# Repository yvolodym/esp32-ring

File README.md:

# esp32-ring

https://github.com/espressif/esp-idf/tree/v5.4/examples/peripherals/lcd/i2c_oled/main

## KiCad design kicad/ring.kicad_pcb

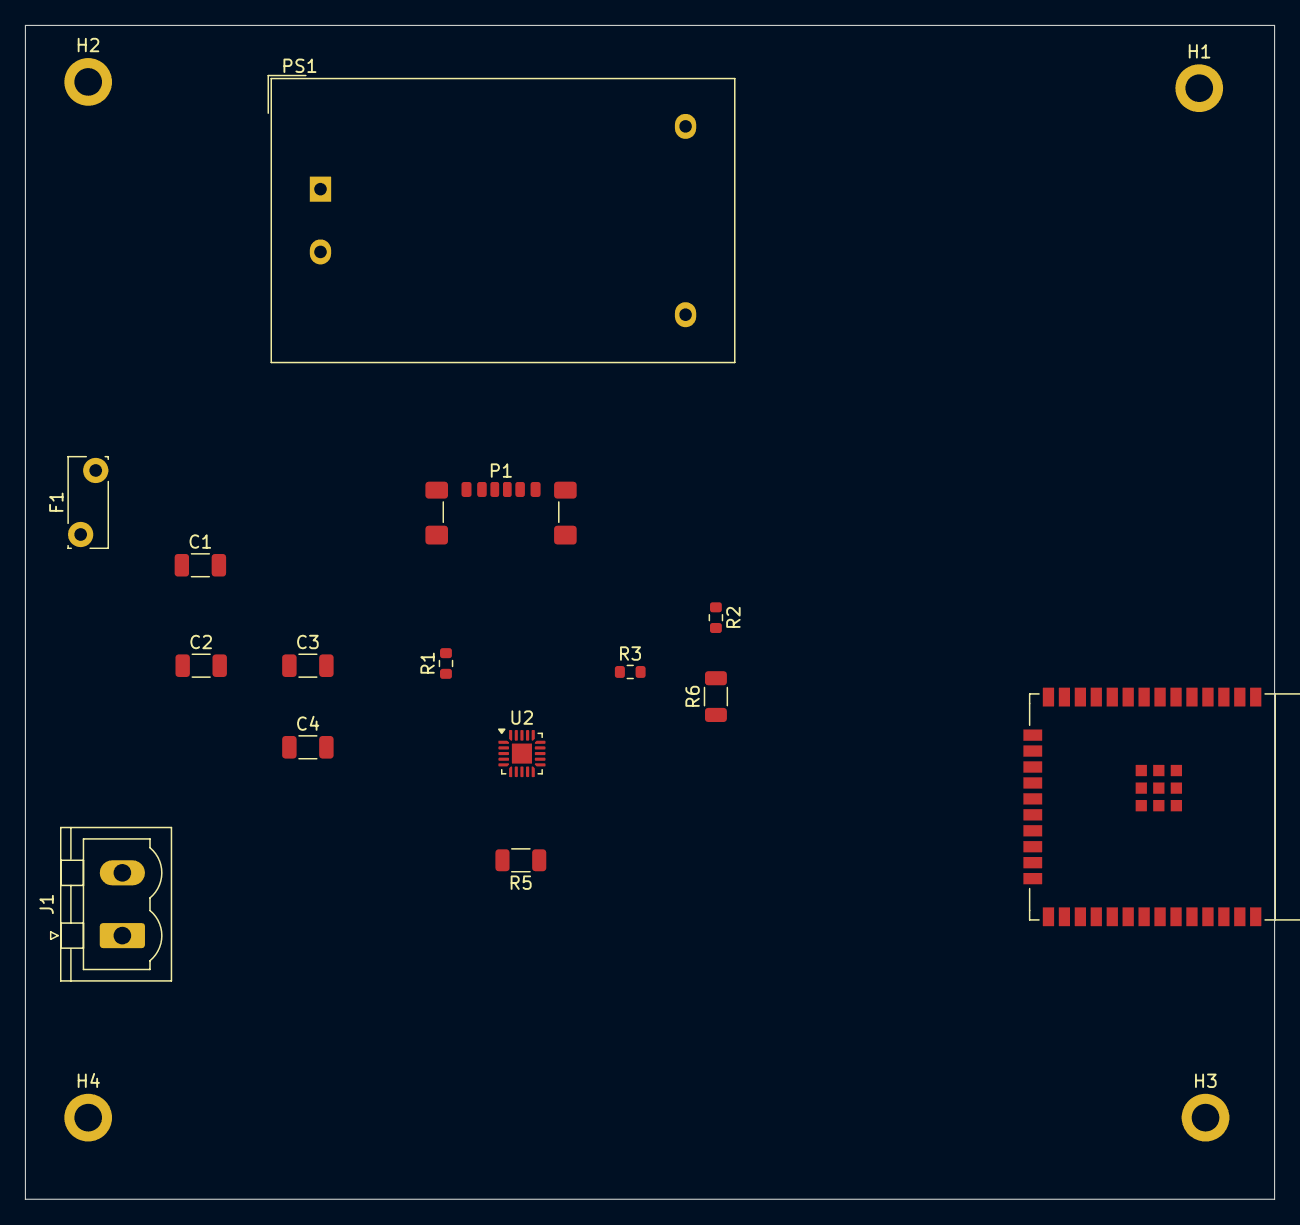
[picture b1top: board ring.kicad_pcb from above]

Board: 2 copper layers, 99.5 x 93.5 mm, 19 parts (0 on the bottom side), 9 nets, no tracks yet.

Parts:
C1: 1µF; C_1206_3216Metric
C2: 100nF; C_1206_3216Metric
C3: 4,7µF; C_1206_3216Metric
C4: 0,1µF; C_1206_3216Metric
F1: Fuse; Fuse_Bourns_MF-RG300
H1, H2, H3, H4: MountingHole; MountingHole_2.2mm_M2_DIN965_Pad
J1: Conn_01x02; PhoenixContact_MSTBVA_2,5_2-G_1x02_P5.00mm_Vertical
P1: USB_C_Plug_USB2.0; USB_C_Receptacle_GCT_USB4135-GF-A_6P_TopMnt_Horizontal
PS1: HLK-PM01; Converter_ACDC_Hi-Link_HLK-PMxx
R1: 5.1K; R_0603_1608Metric
R2: 22K; R_0603_1608Metric
R3: 47K5; R_0603_1608Metric
R5: 2K; R_1206_3216Metric
R6: 10K; R_1206_3216Metric
U1: ESP32-WROOM-E; ESP32-WROOM-32E
U2: CP2102N-Axx-xQFN20; QFN-20-1EP_3x3mm_P0.45mm_EP1.6x1.6mm

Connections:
+3.3V: C3.2, C4.2, R5.2, U2.6 (VDD), U2.7 (VREGIN)
+5V: C1.1, C2.1, P1.A9 (VBUS), P1.B9 (VBUS), R2.1
GND: C1.2, C2.2, C3.1, C4.1, P1.A12 (GND), P1.B12 (GND), P1.S1 (SHIELD), R1.1, R3.2, R6.2, U1.1 (GND), U1.15 (GND), U1.38 (GND), U2.3 (GND), U2.12 (GND), U2.21 (GND)
unnamed: F1.1, J1.2
unnamed: P1.A5 (CC), R1.2
unnamed: F1.2, PS1.1 (AC/L)
unnamed: R2.2, R3.1, U2.8 (VBUS)
unnamed: R5.1, U2.16 (~RTS)
unnamed: R6.1, U2.11 (~SUSPEND)

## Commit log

2025-01-08 init
